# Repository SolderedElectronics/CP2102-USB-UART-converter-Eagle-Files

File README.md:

# CP2102 USB-UART adapter Eagle Files
## Image

[CP2102 USB to UART adapter(100033)](https://e-radionica.com/en/usb-uart-adapter-with-cp2102-made-by-e-radionica.html)

## Description and details
This little adapter converts USB communication to UART using Silabs CP2102. Everything is packed on a small board. In addition to standard UART pins arranged in standard order: DTR, RXD, TXD, VCC, CTS, GND, other pins from the chip are available on the board: RST, Suspend, Suspend ', RI, DCD, DSR, RTS, CTS.

In addition, the board is a voltage regulator and a switch, it is possible to determine the output voltage of 3.3V or 5V, depending on the device you are using. Logic UART signal is always 3.3V, but do not worry, 5V devices will work without problems. There are also three LEDs, one for power indicator and one for each direction of UART communication.
 
- Dimensions: 25 x 35 mm
- USB - UART bridge: CP2102
- Input voltage: 5V (USB)
- Output voltage: 3.3V ili 5V
- Logic of UART signal: 3.3V

## Repository content
This repo contains Cadsoft Eagle .sch and .brd files for CO2102 breakout. It also contains schematic in .pdf created from .sch Eagle file. 
Files have been arranged into folders for navigating between different versions of board. 
Tip: layer 200 shows top silkscreen and layer 208 should be bottom silkscreen. tParts and bParts layers are not used in actual PCB. 

## Docs
- [CP2102 adapter product page](https://e-radionica.com/en/usb-uart-adapter-with-cp2102-made-by-e-radionica.html)

## Board versions
- v1.0 REV A - inital published version 

## License info
This product is open-source. Yay!
For any tech questions, contact us at techsupport@e-radionica.com
If you find an Issue, please open one at GitHub. If you can improve our product, fork us.

e-radionica.com Team.

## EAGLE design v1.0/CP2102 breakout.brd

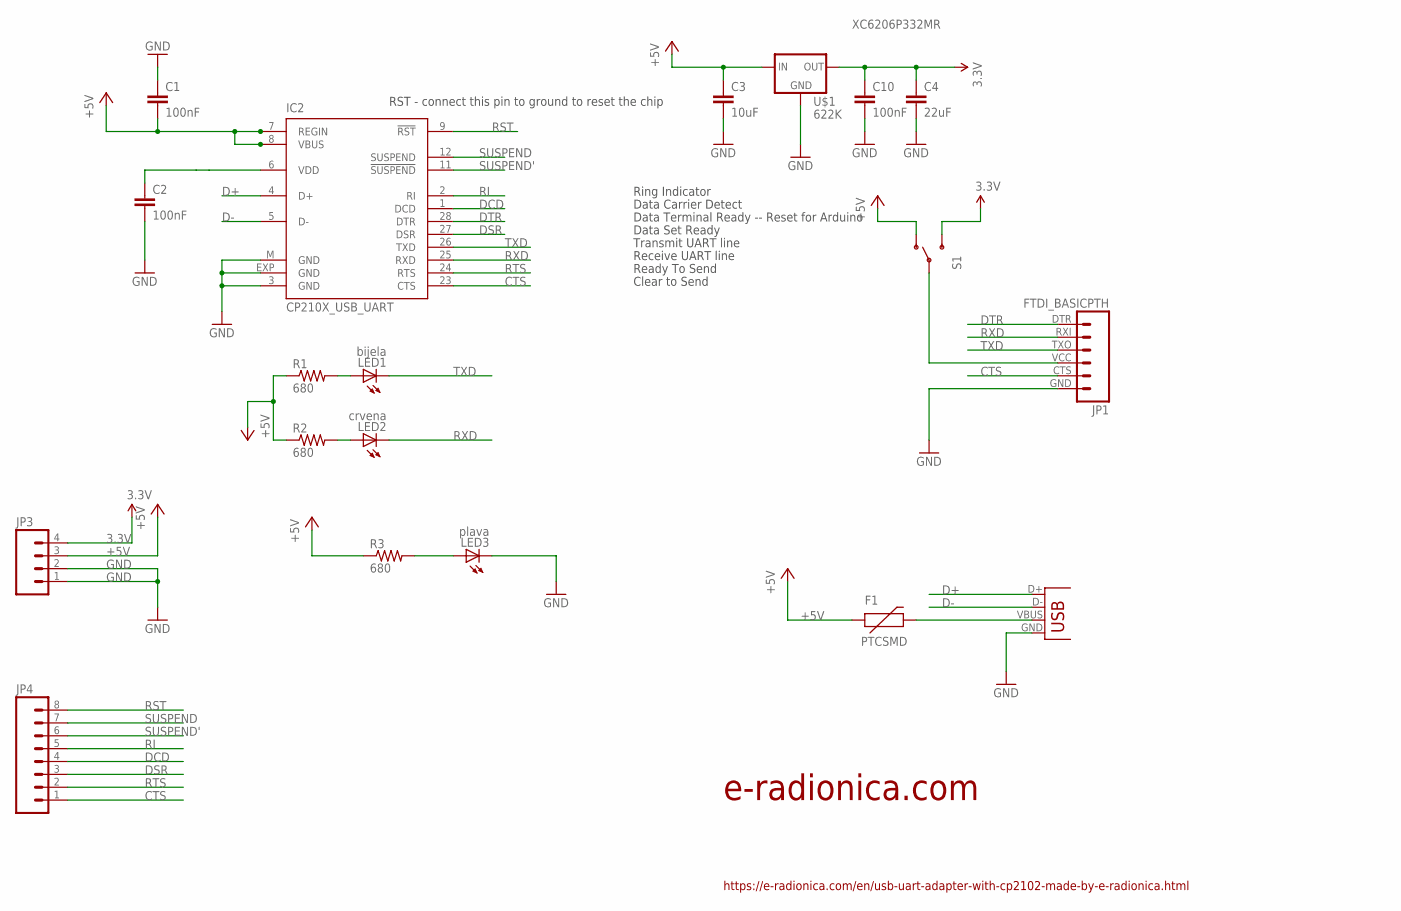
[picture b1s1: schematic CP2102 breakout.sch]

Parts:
C1, C2, C10: 100nF; 0603-CAP
C3: 10uF; C3216
C4: 22uF; C3216
F1: PTCSMD; PTC-1206
IC2: CP210X_USB_UART; MLP28
JP1: FTDI_BASICPTH; FTDI_BASIC
JP3: M04PTH; 1X04
JP4: M081X08; 1X08
LED1: bijela; CHIP-LED0805
LED2: crvena; CHIP-LED0805
LED3: plava; CHIP-LED0805
R1, R2, R3: 680; 0603-RES
S1: SWITCH-SPST-SMD-A
U$1: 622K; 662K
X1: USB-MICROB

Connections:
3.3V: C4.1, C10.1, JP3.4, S1.3 (S), U$1.OUT
+5V: C1.2, C3.1, F1.1, IC2.7 (REGIN), IC2.8 (VBUS), JP3.3, R1.1, R2.1, R3.1, S1.1 (O), U$1.IN
CTS: IC2.23 (CTS), JP1.CTS (5), JP4.1
D+: IC2.4 (D+), X1.D+
D-: IC2.5 (D-), X1.D-
DCD: IC2.1 (DCD), JP4.4
DSR: IC2.27 (DSR), JP4.3
DTR: IC2.28 (DTR), JP1.DTR (1)
GND: C1.1, C2.2, C3.2, C4.2, C10.2, IC2.3 (GND), IC2.EXP (GND), IC2.M (GND), JP1.GND (6), JP3.1, JP3.2, LED3.C, U$1.GND, X1.GND
unnamed: LED1.A, R1.2
unnamed: LED2.A, R2.2
unnamed: LED3.A, R3.2
unnamed: C2.1, IC2.6 (VDD)
RI: IC2.2 (RI), JP4.5
RST: IC2.9 (!RST), JP4.8
RTS: IC2.24 (RTS), JP4.2
RXD: IC2.25 (RXD), JP1.RXI (2), LED2.C
SUSPEND: IC2.12 (SUSPEND), JP4.7
SUSPEND': IC2.11 (!SUSPEND), JP4.6
TXD: IC2.26 (TXD), JP1.TXO (3), LED1.C
VBUS: F1.2, X1.VBUS
VCC: JP1.VCC (4), S1.2

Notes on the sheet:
RST - connect this pin to ground to reset the chip
Clear to Send
Data Terminal Ready -- Reset for Arduino
Data Set Ready
Transmit UART line
Receive UART line
Data Carrier Detect
Ring Indicator
Ready To Send
XC6206P332MR
https://e-radionica.com/en/usb-uart-adapter-with-cp2102-made-by-e-radionica.html
e-radionica.com

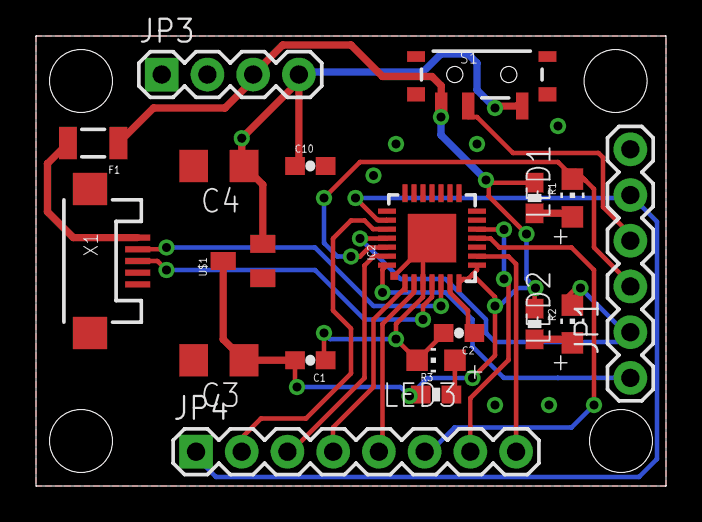
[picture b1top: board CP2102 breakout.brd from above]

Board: 2 copper layers, 35.0 x 25.0 mm, 23 parts (0 on the bottom side), 22 nets.

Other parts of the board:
U$2: OSH3MM
U$3: NOVI_LOGO-4MM
U$4: LUDI_LOGO_BACK
U$5: E-RADIONICA.COM_MADE_IN_BACK!

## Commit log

2017-01-11 Initial
2017-01-11 Formatting changed
2017-01-11 You don't need this one :)
    Deleted temp Eagle files
2018-11-26 README update
2019-02-04 Fix docs link.

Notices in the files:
parts and their libraries:
SparkFun: Licensing: CC v3.0 Share-Alike You are welcome to use this library for commercial purposes.
SparkFun-DigitalIC: Licensing: Creative Commons ShareAlike 4.0 International - https://creativecommons.org/licenses/by-sa/4.0
